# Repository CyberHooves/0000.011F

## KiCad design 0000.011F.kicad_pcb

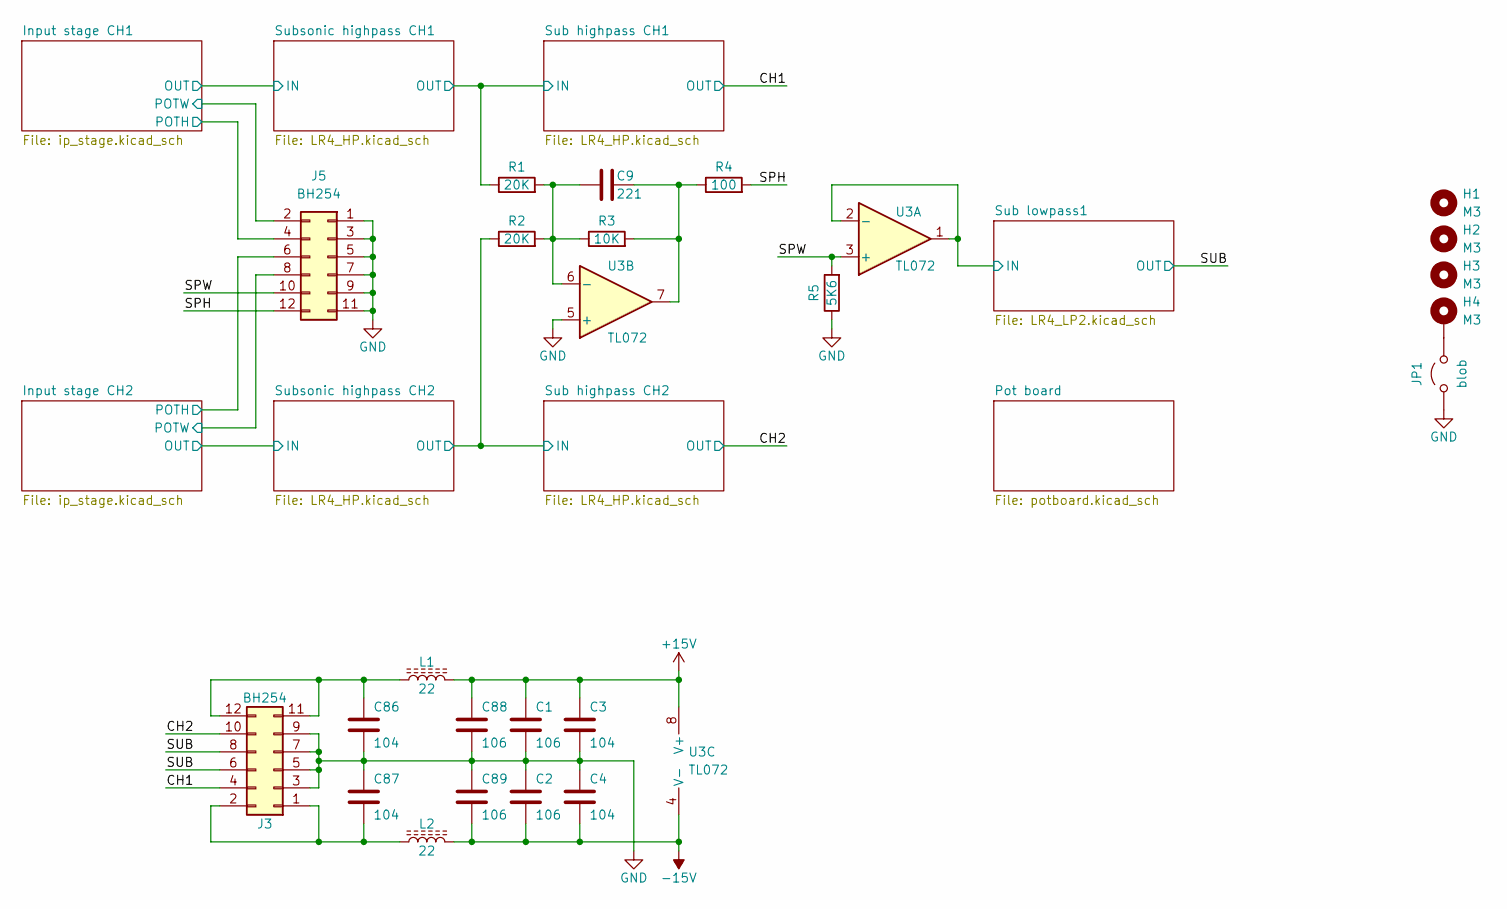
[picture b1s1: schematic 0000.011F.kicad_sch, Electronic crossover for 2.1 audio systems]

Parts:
C1, C2, C88, C89: 106; C_1210_3225Metric
C3, C4, C86, C87: 104; C_0805_2012Metric
C9: 221; C_0805_2012Metric
H1, H2, H3: M3; MountingHole_3.2mm_M3
H4: M3; MountingHole_3.2mm_M3_Pad
J3, J5: BH254; IDC-Header_2x06_P2.54mm_Vertical
JP1: blob; SolderJumper-2_P1.3mm_Open_RoundedPad1.0x1.5mm
L1, L2: 22; L_1210_3225Metric
R1, R2: 20K; R_0805_2012Metric
R3: 10K; R_0805_2012Metric
R4: 100; R_0805_2012Metric
R5: 5K6; R_0805_2012Metric
U3: TL072; SOIC-8_3.9x4.9mm_P1.27mm

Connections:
+15V: C1.1, C3.1, C88.1, L1.2, U3.8 (V+); also elsewhere on the board
-15V: C2.2, C4.2, C89.2, L2.2, U3.4 (V-); also elsewhere on the board
/CH1: J3.4; also elsewhere on the board
/CH2: J3.10; also elsewhere on the board
/Input stage CH1/POTH: J5.4; also elsewhere on the board
/Input stage CH1/POTW: J5.2; also elsewhere on the board
/Input stage CH2/POTH: J5.6; also elsewhere on the board
/Input stage CH2/POTW: J5.8; also elsewhere on the board
/SPH: J5.12, R4.2
/SPW: J5.10, R5.2, U3.3 (+)
/SUB: J3.6, J3.8; also elsewhere on the board
/Sub highpass CH1/IN: R1.1; also elsewhere on the board
/Sub highpass CH2/IN: R2.1; also elsewhere on the board
/Sub lowpass1/IN: U3.1, U3.2 (-); also elsewhere on the board
GND: C1.2, C2.1, C3.2, C4.1, C86.2, C87.1, C88.2, C89.1, J3.3, J3.5, J3.7, J3.9, J5.1, J5.3, J5.5, J5.7, J5.9, J5.11, JP1.1 (A), R5.1, U3.5 (+); also elsewhere on the board
unnamed: C9.2, R3.2, R4.1, U3.7
unnamed: C87.2, J3.1, J3.2, L2.1
unnamed: C86.1, J3.11, J3.12, L1.1
unnamed: H4.1, JP1.2 (B)
unnamed: C9.1, R1.2, R2.2, R3.1, U3.6 (-)

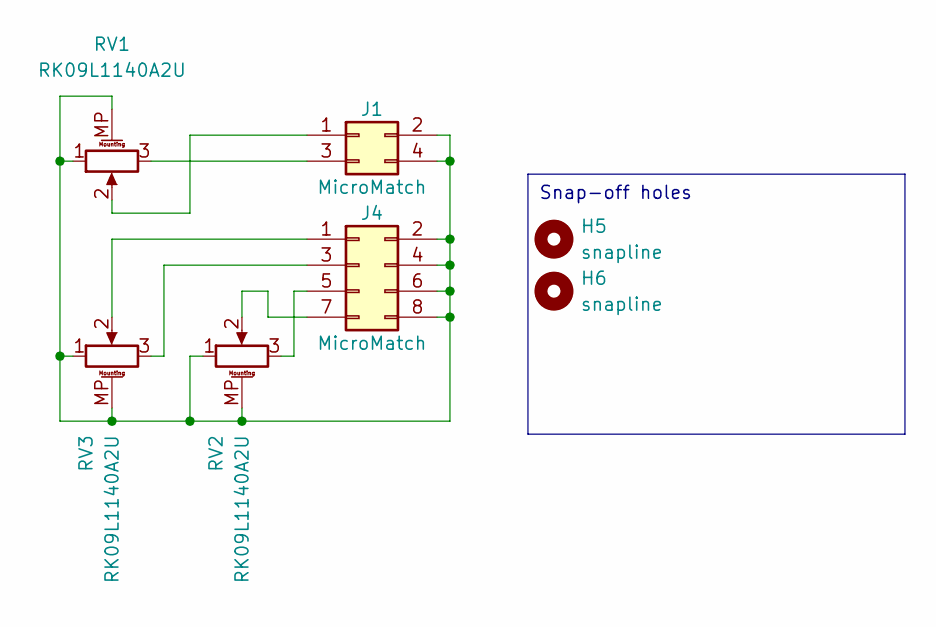
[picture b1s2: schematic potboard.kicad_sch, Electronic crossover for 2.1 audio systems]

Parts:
H5, H6: snapline; SNAPOFF_5x0.6_P1.2
J1: MicroMatch; TE_Micro-MaTch_215079-4_2x02_P1.27mm_Vertical
J4: MicroMatch; TE_Micro-MaTch_215079-8_2x04_P1.27mm_Vertical
RV1, RV2, RV3: RK09L1140A2U; Potentiometer_Alps_RK09L_Single_Vertical

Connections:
unnamed: J1.1, RV1.2
unnamed: J1.2, J1.4, J4.2, J4.4, J4.6, J4.8, RV1.1, RV1.MP (MountPin), RV2.1, RV2.MP (MountPin), RV3.1, RV3.MP (MountPin)
unnamed: J1.3, RV1.3
unnamed: J4.1, RV3.2
unnamed: J4.3, RV3.3
unnamed: J4.5, RV2.3
unnamed: J4.7, RV2.2

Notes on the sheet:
Snap-off holes

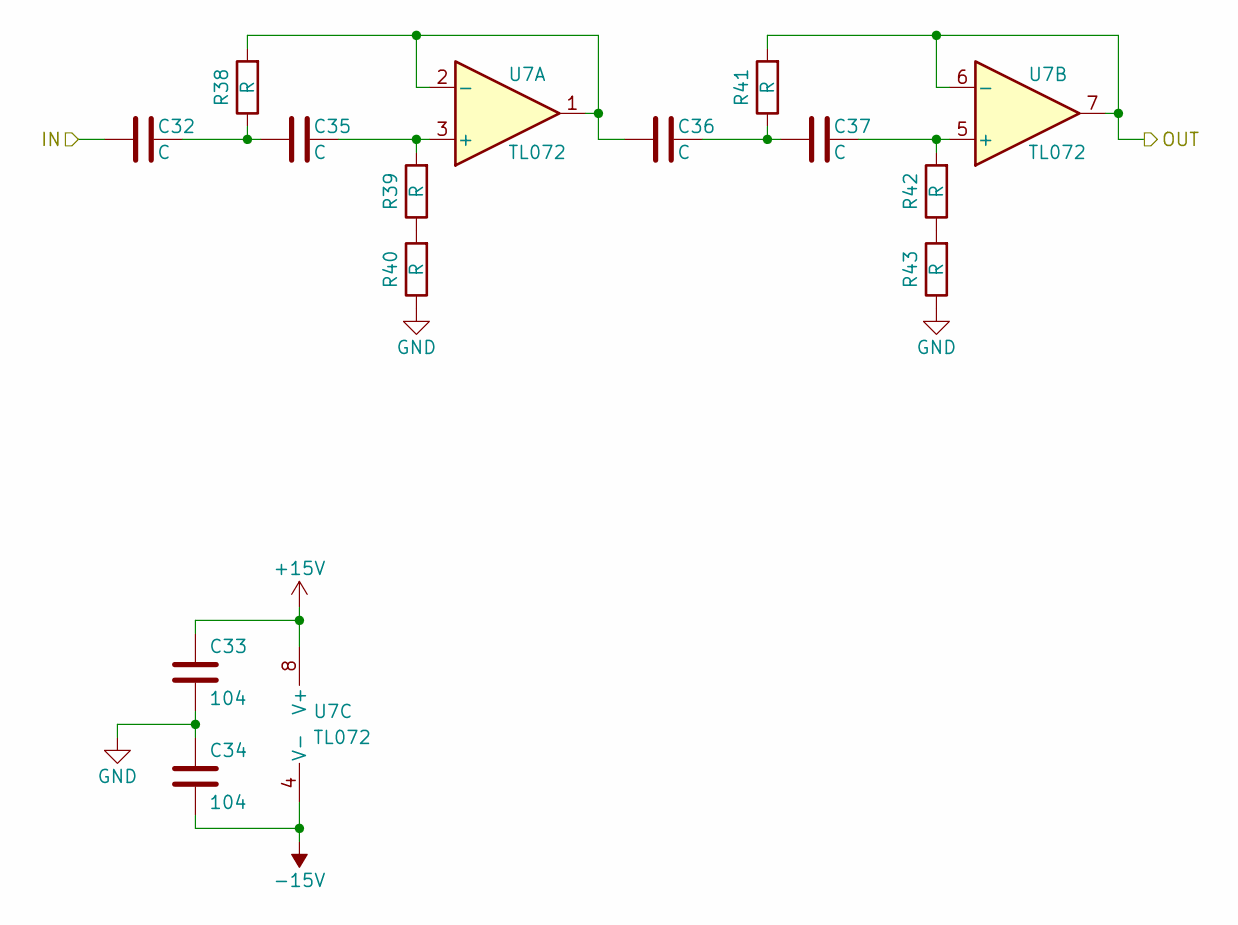
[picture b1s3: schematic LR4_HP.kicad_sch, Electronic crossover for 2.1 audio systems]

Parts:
C32, C35, C36, C37: C; C_Rect_L7.2mm_W7.2mm_P5.00mm_FKS2_FKP2_MKS2_MKP2
C33, C34: 104; C_0805_2012Metric
R38, R39, R40, R41, R42, R43: R; R_0805_2012Metric
U7: TL072; SOIC-8_3.9x4.9mm_P1.27mm

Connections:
+15V: C33.1, U7.8 (V+); also elsewhere on the board
-15V: C34.2, U7.4 (V-); also elsewhere on the board
/CH1: R41.2, U7.6 (-), U7.7; also elsewhere on the board
/Sub highpass CH1/IN: C32.1; also elsewhere on the board
GND: C33.2, C34.1, R40.1, R43.1; also elsewhere on the board
unnamed: C32.2, C35.1, R38.1
unnamed: C36.2, C37.1, R41.1
unnamed: R39.1, R40.2
unnamed: R42.1, R43.2
unnamed: C35.2, R39.2, U7.3 (+)
unnamed: C36.1, R38.2, U7.1, U7.2 (-)
unnamed: C37.2, R42.2, U7.5 (+)

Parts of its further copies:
C38, C41, C42, C43, C74, C77, C78, C79, C80, C83, C84, C85: C; C_Rect_L7.2mm_W7.2mm_P5.00mm_FKS2_FKP2_MKS2_MKP2
C39, C40, C75, C76, C81, C82: 104; C_0805_2012Metric
R44, R45, R46, R47, R48, R49, R68, R69, R70, R71, R72, R73, R74, R75, R76, R77, R78, R79: R; R_0805_2012Metric
U8, U13, U14: TL072; SOIC-8_3.9x4.9mm_P1.27mm

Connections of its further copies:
+15V: C39.1, C75.1, C81.1, U8.8 (V+), U13.8 (V+), U14.8 (V+); also elsewhere on the board
-15V: C40.2, C76.2, C82.2, U8.4 (V-), U13.4 (V-), U14.4 (V-); also elsewhere on the board
/CH2: R47.2, U8.6 (-), U8.7; also elsewhere on the board
/Input stage CH1/OUT: C74.1; also elsewhere on the board
/Input stage CH2/OUT: C80.1; also elsewhere on the board
/Sub highpass CH1/IN: R71.2, U13.6 (-), U13.7; also elsewhere on the board
/Sub highpass CH2/IN: C38.1, R77.2, U14.6 (-), U14.7; also elsewhere on the board
GND: C39.2, C40.1, C75.2, C76.1, C81.2, C82.1, R46.1, R49.1, R70.1, R73.1, R76.1, R79.1; also elsewhere on the board
unnamed: C38.2, C41.1, R44.1
unnamed: C42.2, C43.1, R47.1
unnamed: C74.2, C77.1, R68.1
unnamed: C78.2, C79.1, R71.1
unnamed: C80.2, C83.1, R74.1
unnamed: C84.2, C85.1, R77.1
unnamed: R45.1, R46.2
unnamed: R48.1, R49.2
unnamed: R69.1, R70.2
unnamed: R72.1, R73.2
unnamed: R75.1, R76.2
unnamed: R78.1, R79.2
unnamed: C41.2, R45.2, U8.3 (+)
unnamed: C42.1, R44.2, U8.1, U8.2 (-)
unnamed: C43.2, R48.2, U8.5 (+)
unnamed: C77.2, R69.2, U13.3 (+)
unnamed: C78.1, R68.2, U13.1, U13.2 (-)
unnamed: C79.2, R72.2, U13.5 (+)
unnamed: C83.2, R75.2, U14.3 (+)
unnamed: C84.1, R74.2, U14.1, U14.2 (-)
unnamed: C85.2, R78.2, U14.5 (+)

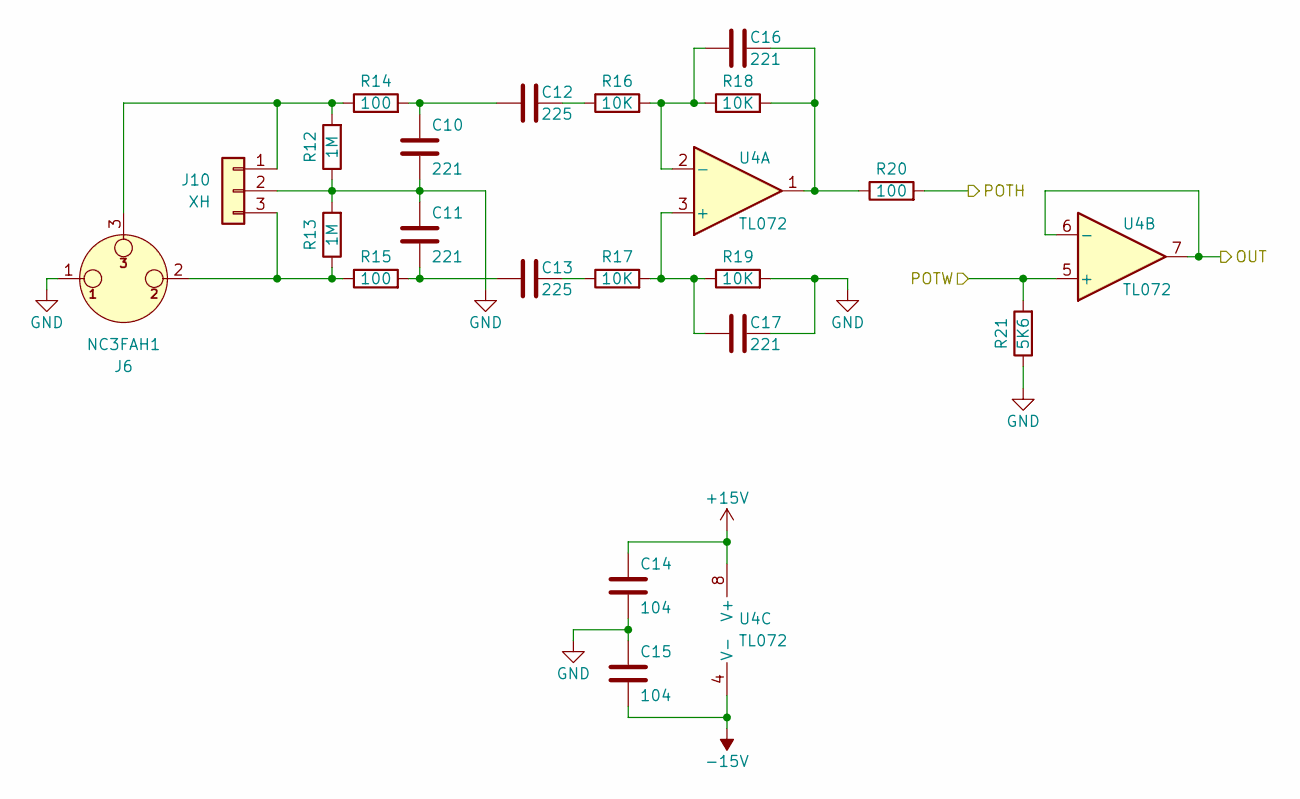
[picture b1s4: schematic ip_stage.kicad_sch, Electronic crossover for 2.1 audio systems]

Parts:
C10, C11, C16, C17: 221; C_0805_2012Metric
C12, C13: 225; C_Rect_L10.3mm_W5.7mm_P7.50mm_MKS4
C14, C15: 104; C_0805_2012Metric
J6: NC3FAH1; Jack_XLR_Neutrik_NC3FAH1_Horizontal
J10: XH; JST_XH_B3B-XH-AM_1x03_P2.50mm_Vertical
R12, R13: 1M; R_0805_2012Metric
R14, R15, R20: 100; R_0805_2012Metric
R16, R17, R18, R19: 10K; R_0805_2012Metric
R21: 5K6; R_0805_2012Metric
U4: TL072; SOIC-8_3.9x4.9mm_P1.27mm

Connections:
+15V: C14.1, U4.8 (V+); also elsewhere on the board
-15V: C15.2, U4.4 (V-); also elsewhere on the board
/Input stage CH1/OUT: U4.6 (-), U4.7; also elsewhere on the board
/Input stage CH1/POTH: R20.2; also elsewhere on the board
/Input stage CH1/POTW: R21.2, U4.5 (+); also elsewhere on the board
GND: C10.2, C11.1, C14.2, C15.1, C17.2, J6.1, J10.2, R12.1, R13.2, R19.2, R21.1; also elsewhere on the board
unnamed: C10.1, C12.1, R14.2
unnamed: C11.2, C13.1, R15.2
unnamed: C12.2, R16.1
unnamed: C13.2, R17.1
unnamed: C16.2, R18.2, R20.1, U4.1
unnamed: J6.3, J10.1, R12.2, R14.1
unnamed: J6.2, J10.3, R13.1, R15.1
unnamed: C17.1, R17.2, R19.1, U4.3 (+)
unnamed: C16.1, R16.2, R18.1, U4.2 (-)

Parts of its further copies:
C18, C19, C24, C25: 221; C_0805_2012Metric
C20, C21: 225; C_Rect_L10.3mm_W5.7mm_P7.50mm_MKS4
C22, C23: 104; C_0805_2012Metric
J8: NC3FAH1; Jack_XLR_Neutrik_NC3FAH1_Horizontal
J12: XH; JST_XH_B3B-XH-AM_1x03_P2.50mm_Vertical
R22, R23: 1M; R_0805_2012Metric
R24, R25, R30: 100; R_0805_2012Metric
R26, R27, R28, R29: 10K; R_0805_2012Metric
R31: 5K6; R_0805_2012Metric
U5: TL072; SOIC-8_3.9x4.9mm_P1.27mm

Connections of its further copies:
+15V: C22.1, U5.8 (V+); also elsewhere on the board
-15V: C23.2, U5.4 (V-); also elsewhere on the board
/Input stage CH2/OUT: U5.6 (-), U5.7; also elsewhere on the board
/Input stage CH2/POTH: R30.2; also elsewhere on the board
/Input stage CH2/POTW: R31.2, U5.5 (+); also elsewhere on the board
GND: C18.2, C19.1, C22.2, C23.1, C25.2, J8.1, J12.2, R22.1, R23.2, R29.2, R31.1; also elsewhere on the board
unnamed: C18.1, C20.1, R24.2
unnamed: C19.2, C21.1, R25.2
unnamed: C20.2, R26.1
unnamed: C21.2, R27.1
unnamed: C24.2, R28.2, R30.1, U5.1
unnamed: J8.3, J12.1, R22.2, R24.1
unnamed: J8.2, J12.3, R23.1, R25.1
unnamed: C25.1, R27.2, R29.1, U5.3 (+)
unnamed: C24.1, R26.2, R28.1, U5.2 (-)

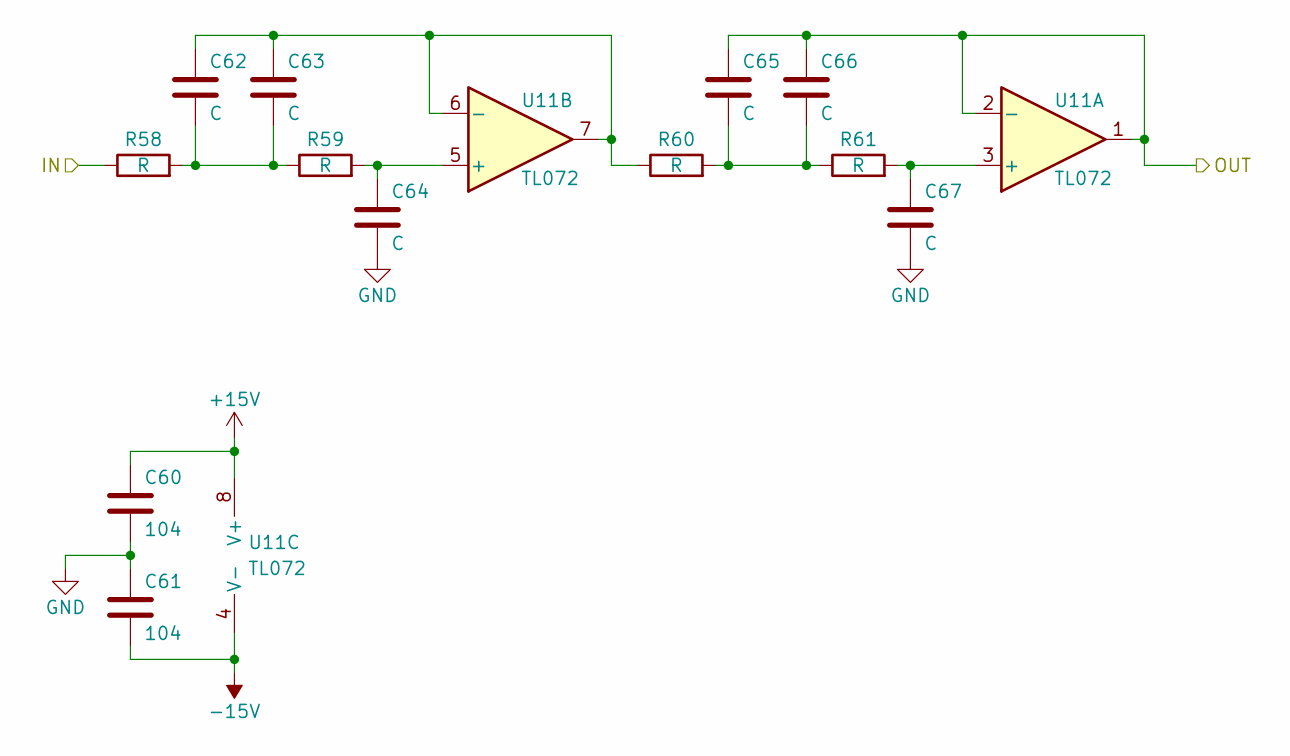
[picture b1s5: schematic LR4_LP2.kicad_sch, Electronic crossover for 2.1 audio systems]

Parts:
C60, C61: 104; C_0805_2012Metric
C62, C63, C64, C65, C66, C67: C; C_Rect_L7.2mm_W7.2mm_P5.00mm_FKS2_FKP2_MKS2_MKP2
R58, R59, R60, R61: R; R_0805_2012Metric
U11: TL072; SOIC-8_3.9x4.9mm_P1.27mm

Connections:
+15V: C60.1, U11.8 (V+); also elsewhere on the board
-15V: C61.2, U11.4 (V-); also elsewhere on the board
/SUB: C65.1, C66.1, U11.1, U11.2 (-); also elsewhere on the board
/Sub lowpass1/IN: R58.1; also elsewhere on the board
GND: C60.2, C61.1, C64.2, C67.2; also elsewhere on the board
unnamed: C62.2, C63.2, R58.2, R59.1
unnamed: C65.2, C66.2, R60.2, R61.1
unnamed: C67.1, R61.2, U11.3 (+)
unnamed: C64.1, R59.2, U11.5 (+)
unnamed: C62.1, C63.1, R60.1, U11.6 (-), U11.7

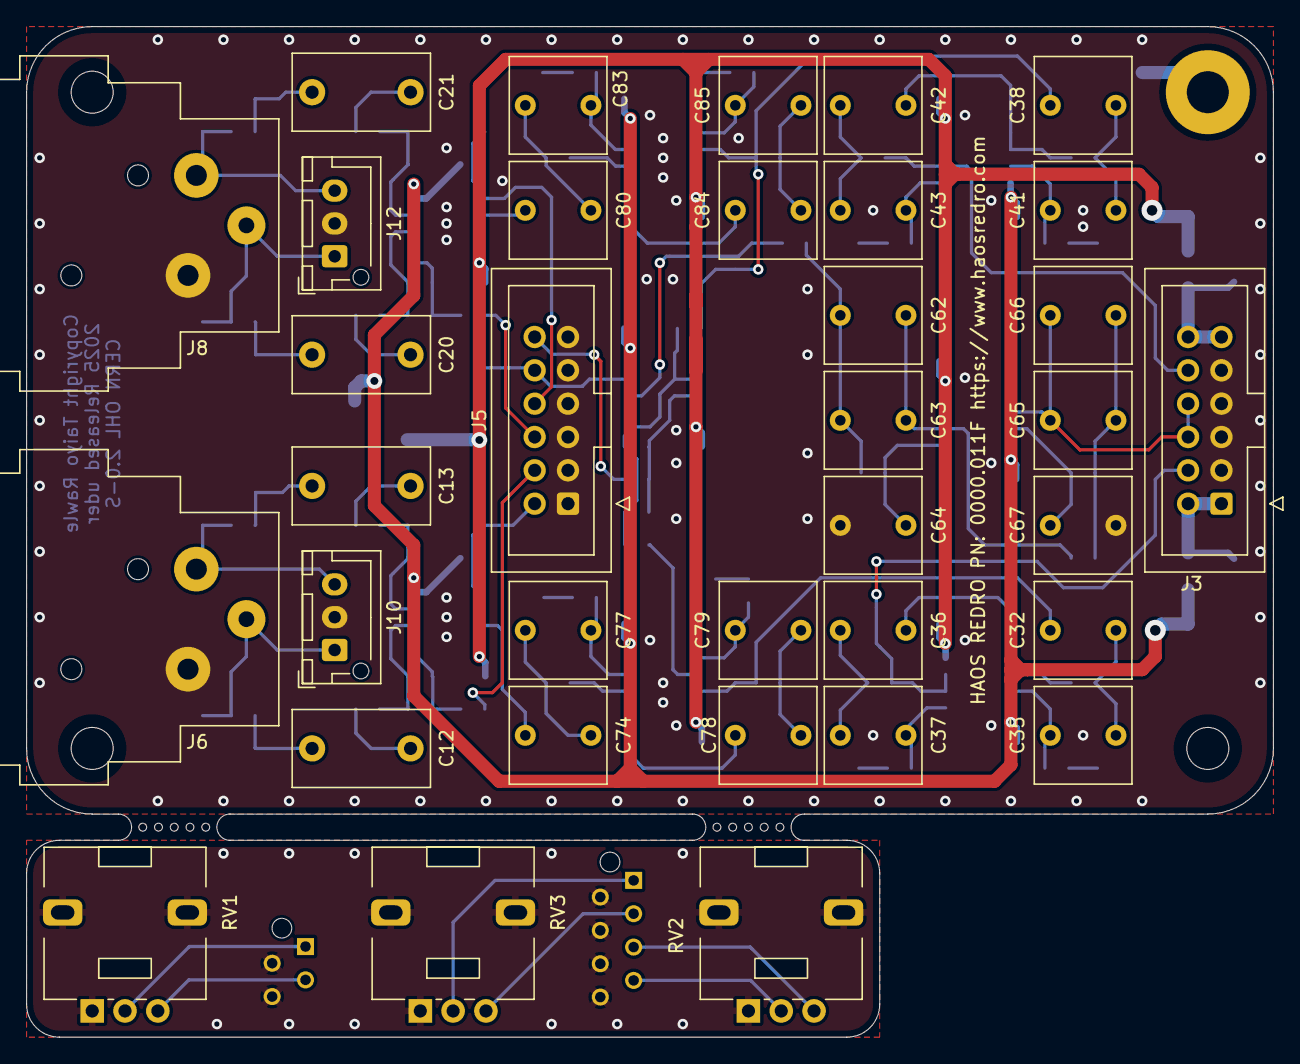
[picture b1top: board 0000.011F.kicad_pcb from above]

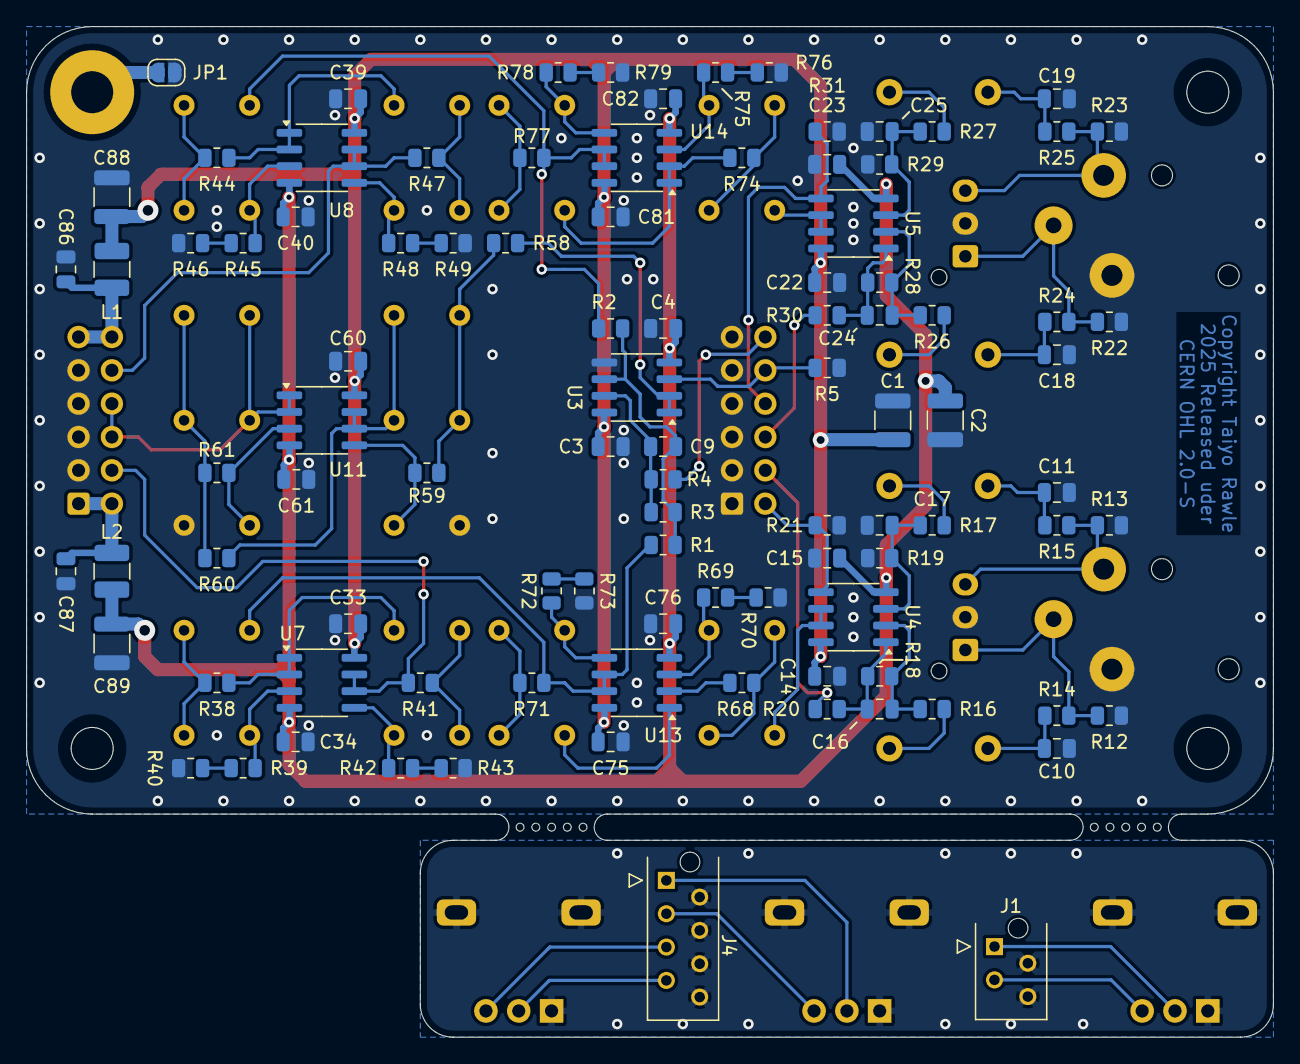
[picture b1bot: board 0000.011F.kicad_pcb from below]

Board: 2 copper layers, 95.0 x 77.0 mm, 138 parts (97 on the bottom side), 80 nets.

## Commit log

2025-07-11 Pot board made smaller using MicroMatch connectors. Snap-off holes tidied up, and gap increased to 2mm for compatibility with some PCB manufacturer's design rules.
2025-07-11 Oops, running DRC would have been sensible. Board outline fixed.

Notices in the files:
0000.011F.kicad_pcb:
Copyright Taiyo Rawle 2025
Released under CERN OHL 2.0-S
CERN OHL 2.0-S
